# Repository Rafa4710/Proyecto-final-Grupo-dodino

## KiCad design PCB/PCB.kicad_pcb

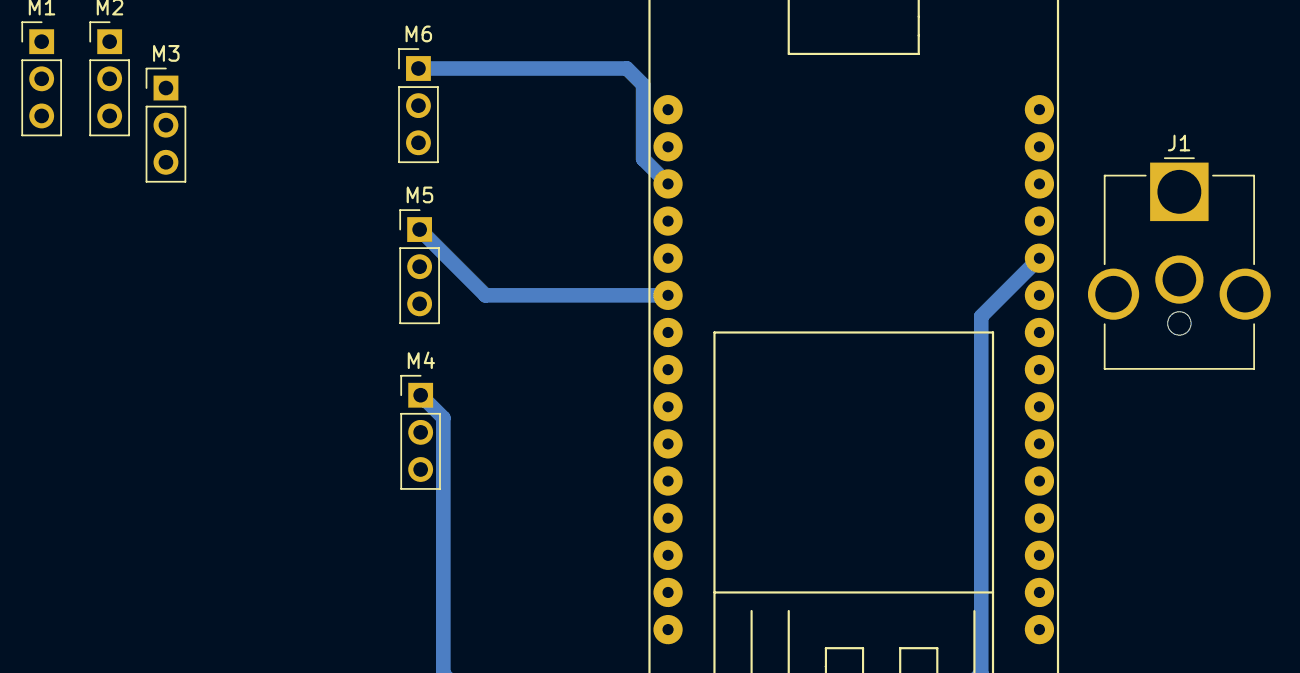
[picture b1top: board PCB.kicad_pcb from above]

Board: 2 copper layers, 8 parts (0 on the bottom side), 8 nets.

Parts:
J1: Barrel_Jack_MountingPin; BarrelJack_CUI_PJ-063AH_Horizontal_CircularHoles
M1, M2, M3, M4, M5, M6: Motor_Servo; PinHeader_1x03_P2.54mm_Vertical
U1: ESP32-Devkit-V1; DOIT_ESP32_Devkit_mirko

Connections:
+12V: J1.1, M1.2 (+), M2.2 (+), M3.2 (+), M4.2 (+), M5.2 (+), M6.2 (+)
GND: J1.2, M1.3 (-), M2.3 (-), M3.3 (-), M4.3 (-), M5.3 (-), M6.3 (-)
PWM1: M3.1 (PWM), U1.21 (IO19)
PWM2: M2.1 (PWM), U1.22 (IO18)
PWM3: M1.1 (PWM), U1.24 (IO17)
PWM4: M5.1 (PWM), U1.25 (IO16)
PWM5: M6.1 (PWM), U1.28 (IO15)
PWM6: M4.1 (PWM), U1.5 (IO14)

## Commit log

2024-05-03 Inicio del esquematico por GIanLuca
2024-05-03 No se que actualizacion fue
2024-05-10 diseño pcb
2024-05-17 Carcasa
2024-05-17 Medida.txt
2024-05-24 Huella stepdown
2024-05-24 .zip
